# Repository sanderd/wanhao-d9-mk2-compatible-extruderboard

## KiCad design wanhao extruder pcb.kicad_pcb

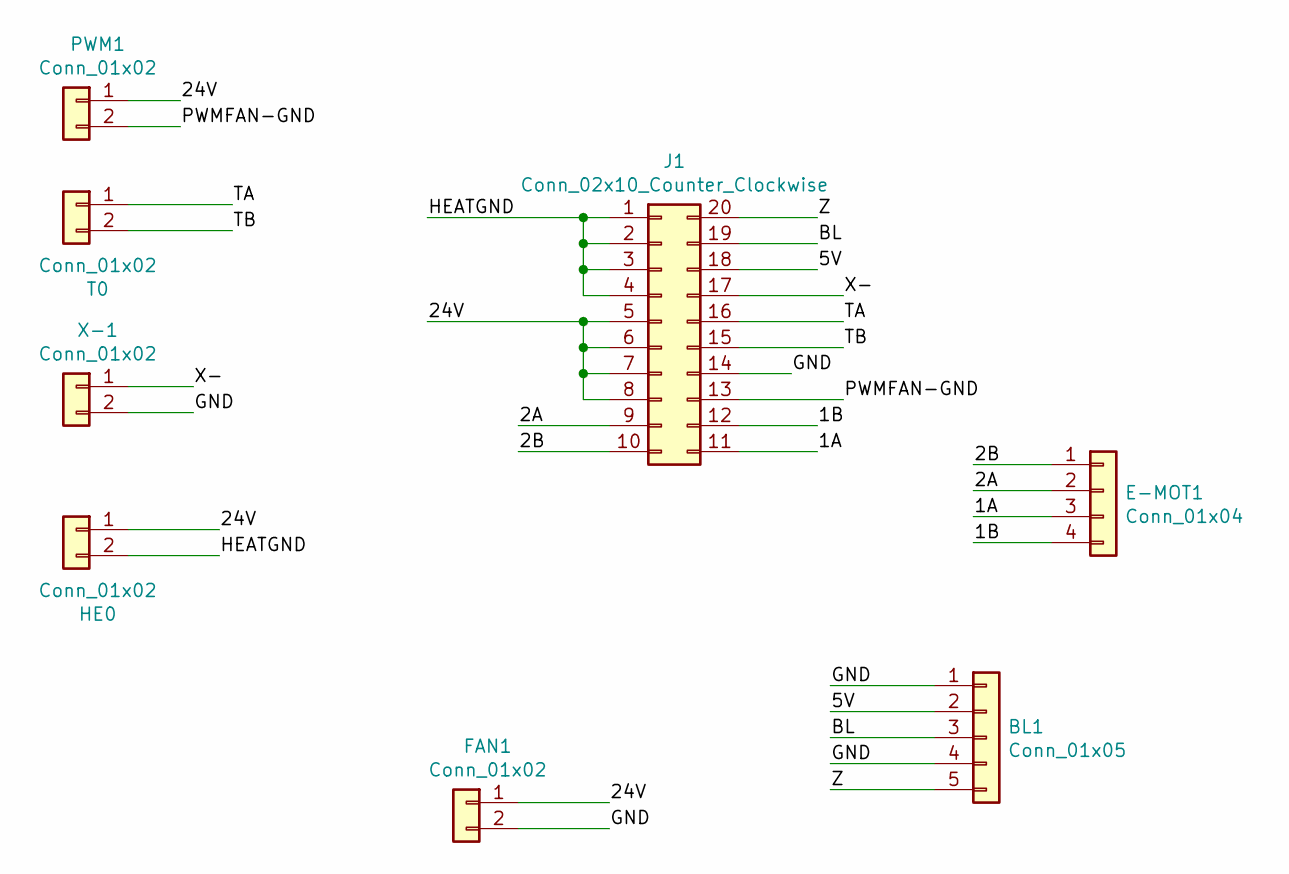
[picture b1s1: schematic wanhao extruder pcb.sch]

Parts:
BL1: Conn_01x05; B5B-ZR
E-MOT1: Conn_01x04; JST_XH_B4B-XH-A_1x04_P2.50mm_Vertical
FAN1: Conn_01x02; JST_XH_B2B-XH-A_1x02_P2.50mm_Vertical
HE0: Conn_01x02; JST_XH_B2B-XH-A_1x02_P2.50mm_Vertical
J1: Conn_02x10_Counter_Clockwise; IDC-Header_2x10_P2.54mm_Vertical_Lock
PWM1: Conn_01x02; JST_XH_B2B-XH-A_1x02_P2.50mm_Vertical
T0: Conn_01x02; JST_XH_B2B-XH-A_1x02_P2.50mm_Vertical
X-1: Conn_01x02; JST_XH_B2B-XH-A_1x02_P2.50mm_Vertical

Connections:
/1A: E-MOT1.3, J1.11
/1B: E-MOT1.4, J1.12
/2A: E-MOT1.2, J1.9
/2B: E-MOT1.1, J1.10
/5V: BL1.2, J1.18
/24V: FAN1.1, HE0.1, J1.5, J1.6, J1.7, J1.8, PWM1.1; also elsewhere on the board
/BL: BL1.3, J1.19
/GND: BL1.1, BL1.4, FAN1.2, J1.14, X-1.2
/HEATGND: HE0.2, J1.1, J1.2, J1.3, J1.4; also elsewhere on the board
/PWMFAN-GND: J1.13, PWM1.2
/TA: J1.16, T0.1
/TB: J1.15, T0.2
/X-: J1.17, X-1.1
/Z: BL1.5, J1.20

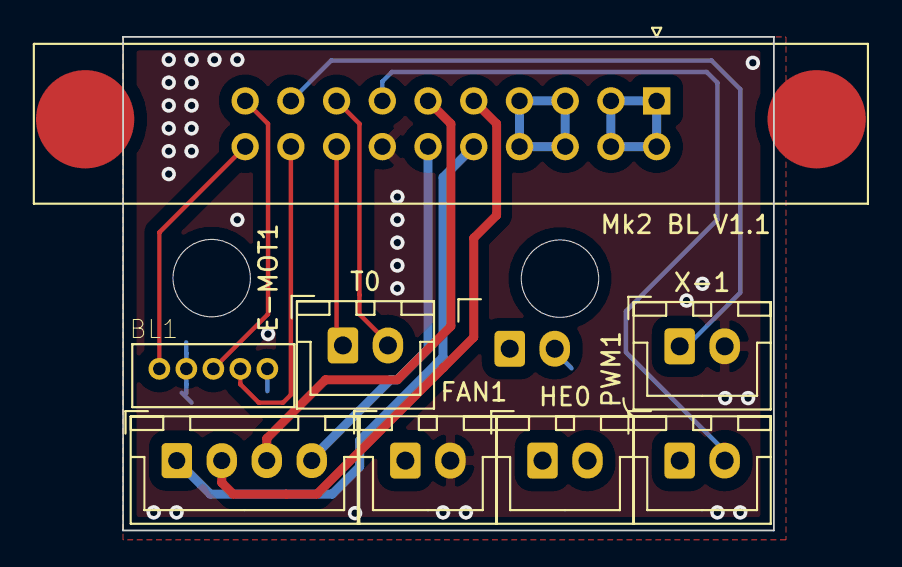
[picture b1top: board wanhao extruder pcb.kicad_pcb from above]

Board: 2 copper layers, 36.2 x 27.4 mm, 9 parts (0 on the bottom side), 14 nets.

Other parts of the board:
HE0#2: Conn_01x02; JST_XH_B2B-XH-A_1x02_P2.50mm_Vertical

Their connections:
/24V: HE0#2.1; also elsewhere on the board
/HEATGND: HE0#2.2; also elsewhere on the board

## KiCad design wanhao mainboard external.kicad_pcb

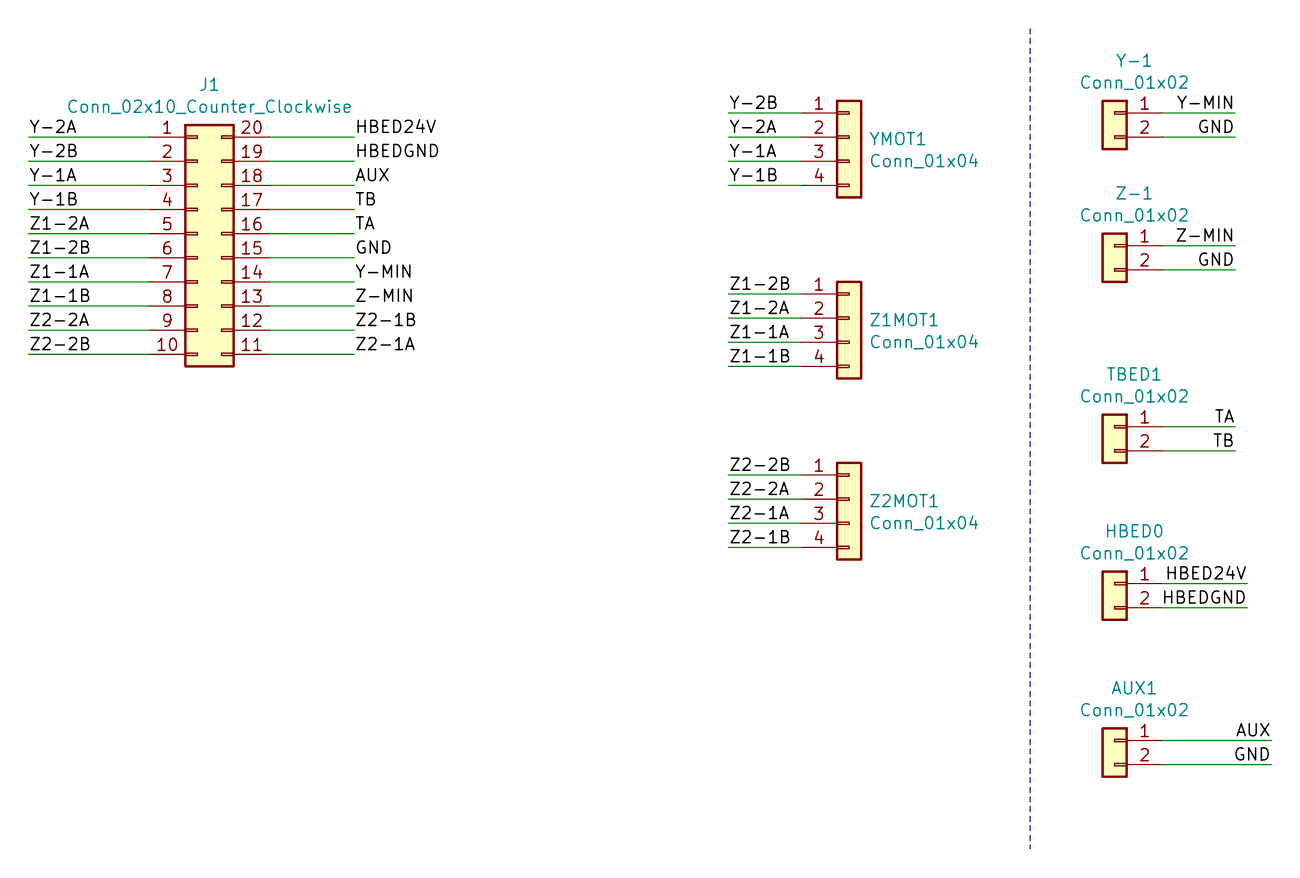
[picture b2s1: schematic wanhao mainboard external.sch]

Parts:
AUX1: Conn_01x02; JST_XH_B2B-XH-A_1x02_P2.50mm_Vertical
HBED0: Conn_01x02; JST_XH_B2B-XH-A_1x02_P2.50mm_Vertical
J1: Conn_02x10_Counter_Clockwise; IDC-Header_2x10_P2.54mm_Vertical_Lock
TBED1: Conn_01x02; JST_XH_B2B-XH-A_1x02_P2.50mm_Vertical
Y-1: Conn_01x02; JST_XH_B2B-XH-A_1x02_P2.50mm_Vertical
YMOT1: Conn_01x04; JST_XH_B4B-XH-A_1x04_P2.50mm_Vertical
Z1MOT1, Z2MOT1: Conn_01x04; JST_XH_B4B-XH-A_1x04_P2.50mm_Vertical
Z-1: Conn_01x02; JST_XH_B2B-XH-A_1x02_P2.50mm_Vertical

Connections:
/AUX: AUX1.1, J1.18
/GND: AUX1.2, J1.15, Y-1.2, Z-1.2
/HBED24V: HBED0.1, J1.20
/HBEDGND: HBED0.2, J1.19
/TA: J1.16, TBED1.1
/TB: J1.17, TBED1.2
/Y-1A: J1.3, YMOT1.3
/Y-1B: J1.4, YMOT1.4
/Y-2A: J1.1, YMOT1.2
/Y-2B: J1.2, YMOT1.1
/Y-MIN: J1.14, Y-1.1
/Z1-1A: J1.7, Z1MOT1.3
/Z1-1B: J1.8, Z1MOT1.4
/Z1-2A: J1.5, Z1MOT1.2
/Z1-2B: J1.6, Z1MOT1.1
/Z2-1A: J1.11, Z2MOT1.3
/Z2-1B: J1.12, Z2MOT1.4
/Z2-2A: J1.9, Z2MOT1.2
/Z2-2B: J1.10, Z2MOT1.1
/Z-MIN: J1.13, Z-1.1

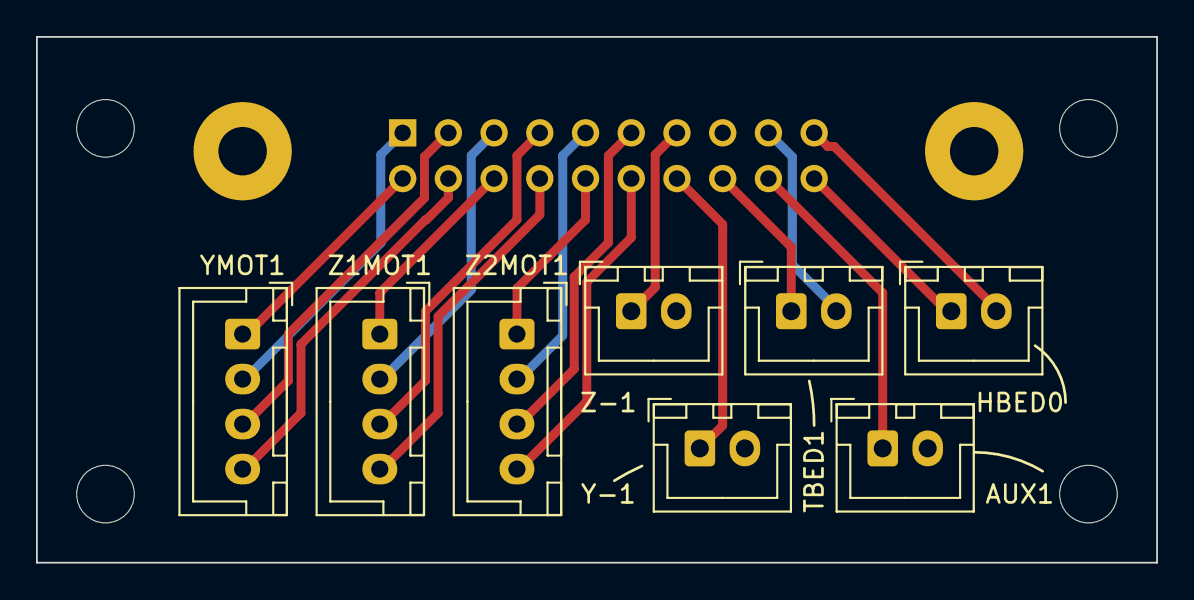
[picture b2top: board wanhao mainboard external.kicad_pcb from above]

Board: 2 copper layers, 62.2 x 29.2 mm, 9 parts (1 on the bottom side), 20 nets.

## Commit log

2019-09-09 Added extender
2019-09-09 Added external board
2019-09-09 Updated schema for extruder pcb (layout)
2019-09-12 Changed text label for extruder board
2019-09-12 Increased sizing of heater trace fills
2019-09-18 Added SKR 1.3 interface cabling
2019-09-18 Updates to extruder board
2019-09-18 Stepper splitter boards
2019-10-12 Updates & missing elements in skr1.3 interface wiring
